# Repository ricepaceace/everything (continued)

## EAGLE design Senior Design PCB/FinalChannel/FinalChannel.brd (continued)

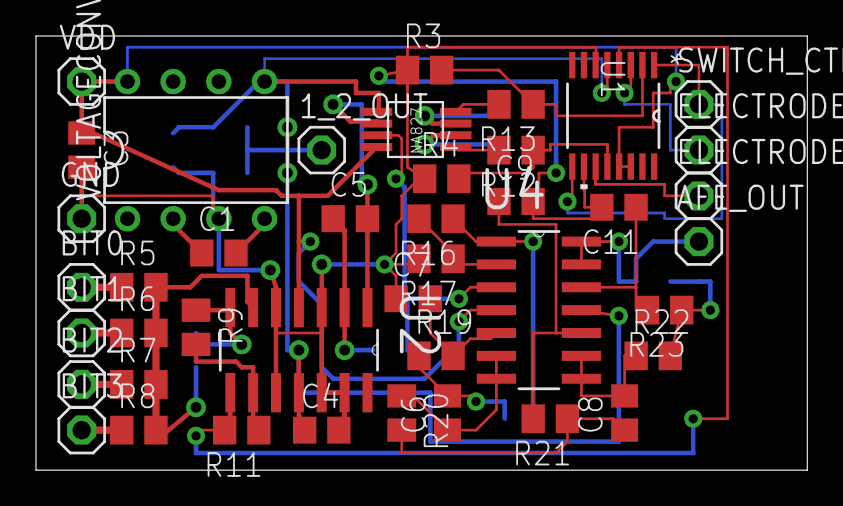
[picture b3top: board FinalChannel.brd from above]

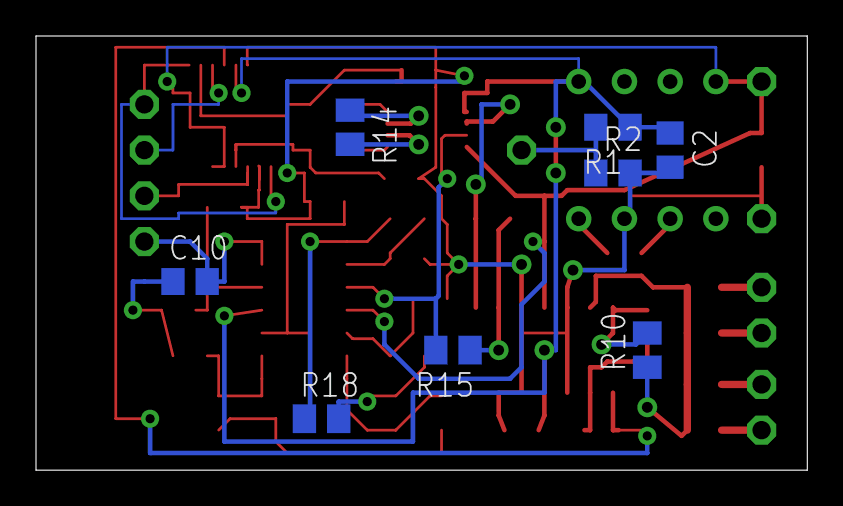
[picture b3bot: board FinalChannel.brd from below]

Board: 2 copper layers, 42.9 x 24.1 mm, 50 parts (8 on the bottom side), 37 nets.

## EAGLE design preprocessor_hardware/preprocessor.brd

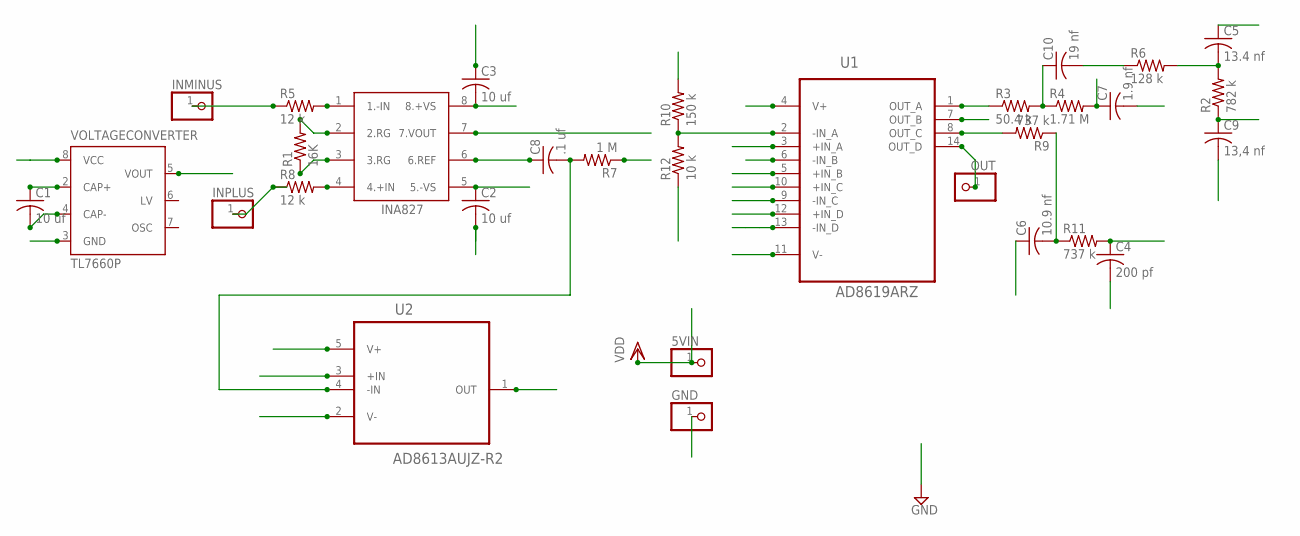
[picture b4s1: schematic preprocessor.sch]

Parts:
5VIN: PINHD-1X1; 1X01
C1, C2, C3: 10 uf; C025-025X050
C4: 200 pf; C025-025X050
C5: 13.4 nf; C025-025X050
C6: 10.9 nf; C025-025X050
C7: 1.9 nf; C025-025X050
C8: .1 uf; C025-025X050
C9: 13,4 nf; C025-025X050
C10: 19 nf; C025-025X050
GND: PINHD-1X1; 1X01
INAMP: INA827
INMINUS: PINHD-1X1; 1X01
INPLUS: PINHD-1X1; 1X01
OUT: PINHD-1X1; 1X01
R1: 16K; 0207/7
R2: 782 k; 0207/7
R3: 50.4 k; 0207/7
R4: 1.71 M; 0207/7
R5, R8: 12 k; 0207/7
R6: 128 k; 0207/7
R7: 1 M; 0207/7
R9, R11: 737 k; 0207/7
R10: 150 k; 0207/7
R12: 10 k; 0207/7
U1: AD8619ARZ; SOIC127P600X175-14N
U2: AD8613AUJZ-R2; SOT95P280X100-5N
VOLTAGECONVERTER: TL7660P; DIL08

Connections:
GND: C2.2, C3.1, C4.2, C7.2, C9.2, GND.1, R12.1, U2.3 (+IN), VOLTAGECONVERTER.3 (GND)
I3: C9.1, R2.1, U1.10 (+IN_C)
I4: C4.1, R11.2, U1.12 (+IN_D)
IAO: INAMP.7 (7.VOUT), R7.1, U1.3 (+IN_A)
IN2: C7.1, R4.2, U1.5 (+IN_B)
I_P: INPLUS.1, R8.1
unnamed: C1.1, VOLTAGECONVERTER.2 (CAP+)
unnamed: C1.2, VOLTAGECONVERTER.4 (CAP-)
unnamed: INAMP.1 (1.-IN), R5.2
unnamed: INAMP.4 (4.+IN), R8.2
unnamed: INAMP.2 (2.RG), R1.2
unnamed: INAMP.3 (3.RG), R1.1
unnamed: C8.2, R7.2, U2.4 (-IN)
unnamed: R10.1, R12.2, U1.2 (-IN_A)
unnamed: C10.1, R3.2, R4.1
unnamed: C5.2, R2.2, R6.2
unnamed: C6.2, R9.1, R11.1
unnamed: INMINUS.1, R5.1
O1: R3.1, R10.2, U1.1 (OUT_A)
O2: C10.2, R6.1, U1.6 (-IN_B), U1.7 (OUT_B)
O3: C5.1, R9.2, U1.8 (OUT_C), U1.9 (-IN_C)
OUT: C6.1, OUT.1, U1.13 (-IN_D), U1.14 (OUT_D)
REF: C8.1, INAMP.6 (6.REF), U2.1 (OUT)
VDD: 5VIN.1, C3.2, INAMP.8 (8.+VS), U1.4 (V+), U2.5 (V+), VOLTAGECONVERTER.8 (VCC)
VDD-: C2.1, INAMP.5 (5.-VS), U1.11 (V-), U2.2 (V-), VOLTAGECONVERTER.5 (VOUT)

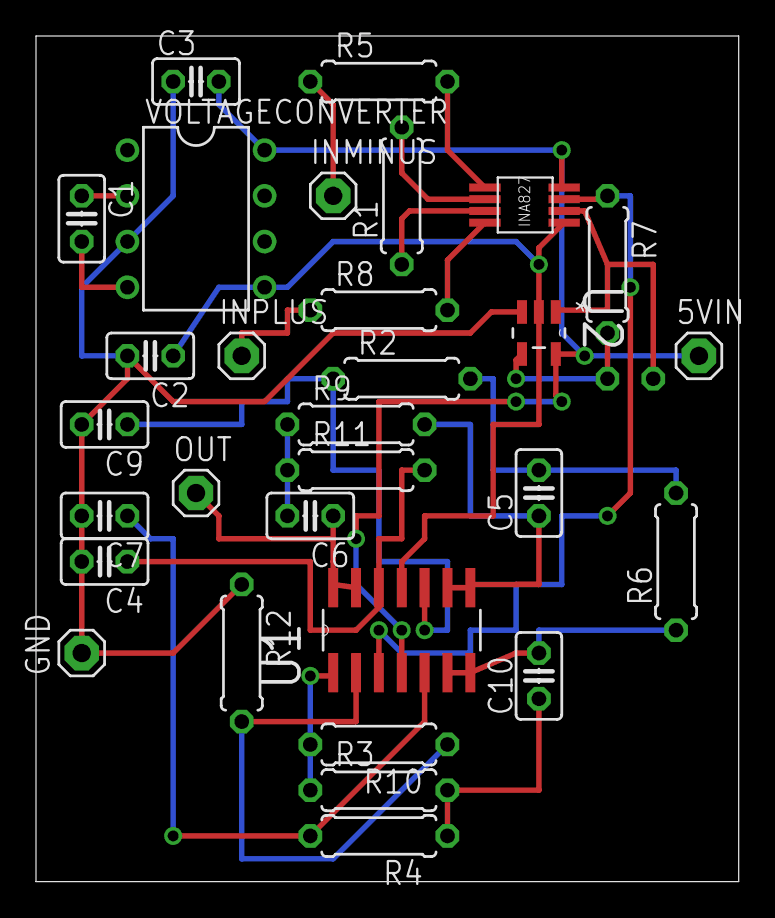
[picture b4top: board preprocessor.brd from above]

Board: 2 copper layers, 39.0 x 47.0 mm, 31 parts (1 on the bottom side), 25 nets.

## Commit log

2016-10-07 added data from sept29 test
2016-10-07 Rename multisite_detect.mat to multisite_detect.m
2016-10-12 Add files via upload
    functional code for detecting atrial and ventricular beats on data from sept29 using only the sum of the channels and set parameters.
2016-10-16 Subdivision based algorithm. Works on some channels, but not all.
2016-10-16 Added new binary search based parameter guesser. It's pretty advanced 😉
2016-10-18 Fixed problem where atrial beats were not always detected due to not big enough zeroing out of ventricular beats by increasting t_blank and l_blank.
2016-10-27 adds empty sketch for c algorithm
2016-10-27 redoes path
2016-10-27 same as previous
2016-10-27 Added channel 1 of normal sinus rythm into progmem
2016-10-27 implements one chamber peak detection
2016-10-27 Delete iaf1_afw.dat
    accessible via internet
2016-10-27 "First draft of translation for GuessParameters 2 to C code"
2016-10-28 Ported CountPeaks to C. The filter needs to be recalculated.
2016-10-28 Few lines need to be analyzed in Guessparameter function with respect to what countPeaks returns
2016-10-29 Fixed many things, but still probably won't compile.
2016-10-29 Fixed bugs. It should actually compile now.
2016-11-01 Add files via upload
    fixed .mat files
2016-11-02 testDecision.m
2016-11-02 testDecision.m
    This script takes in ECG data from a single channel, analyzes the ECG data one sample at a time (in order to best model our real time micro-controller system), and implements decision making on wheth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
2016-11-03 Fixed bug in determining where a stimulation is needed and plot where stimulation occurs for visualization
2016-11-03 fixed a bug where peaks were being over counted
2016-11-06 Added code that makes graph to see if we can get away with no fft
2016-11-06 Deleted physiobank matlab toolbox
2016-11-06 Added new flat-finding algorithm instead of binary search Modified other code to work with it
2016-11-07 Moved data files to same directory + fixed compilation errors
2016-11-07 Bug fixes
    Runs on the Arduino and gives potentially reasonable values for thresholds, but we think it is counting both A and V beats as V beats.
2016-11-11 adds schematic and board files for eagle design of preprocessor
2016-11-15 First draft of creating analog test data with arduino
2016-11-15 adds gerber files for board fabrication
2016-11-15 pushes fab design rule files for future ease of access
2016-11-15 Updated some testing code on analog test arduino file
2016-11-15 Produce analog test data from digital test data
2016-11-20 Added yamPeakFinder and MultisiteDecision
    yamPeakFinder and Multisite Decision incorporate multisite and stimulation functionality to the algirhtm.
2016-11-20 Added serial comm b/n Matlab and Arduino
2016-11-20 Added serial comm capabilities between matlab and arduino
2016-11-20 Moved file
2016-11-20 Add files via upload
    fixed a lot of bugs - still need to adapt yamPeakFinder to look more like CountPeaks (fixed in this update)
2016-11-21 Moved arduino code, fixed one bug Yamin made earlier
2016-11-22 Real time decision works - still fixing bugs with guess parameters
2016-11-22 Fixing bugs with parameter guessing
    choosing between + and - data now; still need to finish and make the same changes in real time decision
2016-11-23 Add files via upload
    added functionality of checking both + an - data
2016-11-23 Matlab code ready for porting to c
2016-11-23 Started porting guessparameters flat-finding algorithm. It may not be up to date with the newest changes.
2016-11-28 Need to add CountPeaks to this .h file
2016-11-28 adds some header files for commonly used values and types
2016-11-28 ports yamPeakFinder.m to c
2016-11-28 fixes typos
2016-11-28 Ported GuessParameters2 and BinarySearch. Added arduinocompat so that it almost compiles with regular gcc with gcc -c -DNO_ARDUINO -x c Arduino.ino
2016-11-28 moved arduino files to arduino
2016-11-28 Switched to using constants in constants.h
2016-11-29 Ported CountPeaks.m
2016-11-29 Refactored
2016-11-29 porting c code
2016-11-30 porting shit from c
2016-11-30 Added a SAMPLE_RATE, MIN_HEARTRATE, and MAX_HEARTRATE to constants.h
2016-11-30 fixing yamins mistakes
2016-12-01 Ported arduino code with the weird error implicit declaration of function
2016-12-01 It compiles!
2016-12-01 Code no runs, but thresholds calculated incorrectly, they are both 0
2016-12-02 Learning thresholds should be working on the microcontroller
2016-12-02 Finished arduinocompat.h so you can actually compile with gcc and run on a computer.
2016-12-02 Modified printed output to prepare for demoing this
2016-12-02 Made multisiteDecision run on the code. It says that the ventricle needs to be stimulated a bunch, which I think is wrong because this is supposed to be healthy heart data, but I haven't run it throu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
2016-12-05 Changed delay, added printing when it finds a beat.
2016-12-05 Added changes to how we stream analog data
2016-12-05 Switched to arduino analog
2016-12-05 Missed change in multisite decision
2016-12-05 Added buffering
2016-12-05 Changed range in matlab data
2016-12-05 Make sure to sample every milisecond when analog reading
2016-12-05 remapped analog values
2016-12-05 Try adding volatile to bufferdata
2016-12-05 Added prelearn code
2016-12-06 Fixed sampling errorgit add yamPeakFinder.h git add yamPeakFinder.h git add yamPeakFinder.h Demo is workable, can use some refinement
2016-12-07 Switched to circular buffers. Should reduce the number of dropped samples.
2016-12-09 adds all the shit for FPGA tools
2017-01-18 added pulse generator hardware schematic
2017-01-21 Added simple voting for pacing
2017-01-21 Preliminary version of polling stimulation completed
2017-01-21 Data used for learning during the first semester demo
2017-01-23 Moved matlab files to matlab folder, added gitignore
2017-01-23 Removed DS_Store
2017-01-23 Remove clutter
2017-01-26 added LearnLengths.m
    Added k-means based algorithm for learning lengths; not really integrated with anything else yet.
2017-01-26 Add files via upload
    uses LearnLengths
2017-01-27 Added simple n/2 polling to C
2017-02-02 README
    This folder will contain all the data that Dr.Greet gave us in early Feburary 2017. It should contain Sinus, atrial flutter, afib, etc.
2017-02-02 Data given to us by Dr. Greet
2017-02-08 Add files via upload
    This branch is for fixing the corner case where the atria are taller than the ventricles
2017-02-08 Update and rename GuessParameters2.m to LearnParameters.m
    uses LearnLengths and tries different lengths for +/- data
2017-02-08 Update LearnLengths.m
    outputs two lengths/chamber for +/- data
2017-02-08 Update multisite_detect.m
    now uses LearnParameters
2017-02-08 Add files via upload
    both main files now use simple versions of LearnParameters and LearnLengths that try different lengths for +/- data but always do ventricles first.
2017-02-08 Added learn lenghts except k-means
2017-02-08 Added untested kmeans
2017-02-15 length learning with k-means works! Not yet integrated though.
2017-02-15 Integrated LearnLengths, add cap to # iterations in k-means. Not sure if it works on all the channels though.
2017-02-23 Added resize to circular buffer
2017-02-26 bugfix
2017-02-27 added weighted polling and fixed overstimulation
    Re-weighting happens a fixed length of time (100ms) after the first of a potential batch of peaks is detected. Uses those 100 ms to determine if a beat occurred, figures out which channels were corre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
    Could potentially use this for stimulation decision to reduce latency by keeping track of the times of globally determined beats
2017-02-28 reorganizes stuff
2017-02-28 adds src for hls design
2017-02-28 Adds finished Vivado HLS Project, including exported IP
2017-02-28 adds screenshots from vivado HLS process
2017-02-28 removes extra screen shot
2017-02-28 adds source files for vivado and sdk, as well as full vivado project
2017-02-28 adds sdk test project to ensure all hardware components function as desired
2017-02-28 moves files around
2017-02-28 adds full system demo project
2017-02-28 commits the stuff i didn't realize wasn't included
2017-03-01 reformatted structs to match others
2017-03-01 stuff for testing/demo
2017-03-19 Add files via upload
    Successful fix of corner case in non-real-time code; started work on real-time
2017-03-20 Real time corner case fix
    It works, but not great yet - need to figure out the right way to delay the decision for the type of peak that is being evaluated second. Probably not using PreVARP/PostVARP/PreAVRP/PostAVRP correctl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
2017-03-29 Committing final arduino test code for showcase
2017-03-29 "Arduino test shit"
2017-03-31 fuck me
2017-04-06 ECE Affiliates day streaming code
2017-04-06 Added Arduino code for showcase (untested)
2017-04-06 random file update
2017-04-08 bad commit message
2017-04-08 Changed outlier removal, sign bug fixed
2017-04-08 Fixed off-by-one weighting bug in kmeans
2017-04-08 Reduced upper limit on allowed peaks to remove outliers. TODO: port statistics-based outlier removal code from Matlab
2017-04-08 Made code fit on small arduino and mega
2017-04-10 adds recent software work
2017-04-10 Fixed version for Arduino pro mini
2017-04-12 Changed Arduino code for showcase to zero out channels. Untested.
2017-04-12 Change from mask to zeroed bools
2017-04-19 Added BOMs, versions for assembly instructions
2017-04-27 Added Latex paper
2017-04-27 Changed bibliography and citations to use bibtex, other minor changes.
2017-04-27 ported more
2017-04-27 Finished porting. Updated graphs with real data
2017-04-27 Aded fpga
2017-04-27 Fixed authors
2017-04-27 More editing, schematic
2017-04-28 Philip's revisions of the first 2.75 pages
2017-04-28 Yamin's changes to matlab code that was used to generate plots for apepr
2017-04-28 Yamin's edits on the ??? and TODO
2017-04-28 Added pdf from Yamin's last edits.
2017-04-28 Made some of benhaam's recommended changes
2017-04-28 Fixed a small typo
2017-04-29 Added figure showing widths and heights.
2017-04-29 Philip finished revising
2017-04-29 adds final asic report and image
2017-04-29 Used to generate test results in our poster
    (using multisite_detect for detection accuracy and multisiteDecision for stimulation accuracy)
2017-04-29 Minor changes to paper
2017-04-29 Minor arduino changes
2017-04-29 Deleted unused files
2017-04-29 Made it more math-y
2017-04-29 Fixed some misspellings, improved next steps
2017-04-29 Added summary, minor changes to paper
2017-04-29 Added Daniel's comments
2017-04-29 Added comments and homogenized variable names
2017-04-30 Incoorperating Joe and benhaam's latest changes
2017-04-30 Fixed minor citation error and added Yamin's comments to the Matlab code
2017-05-01 Added what I could of Behnaam's changes
2017-05-01 Regorganized and documents hardware files
2017-05-01 comments code
2017-05-01 Low latency version
    This version of the code attains latencies under 50 ms, but it may struggle more if the channels are out of sync.
2017-05-01 Made some quick changes before sending Benhaam interation 3
2017-05-01 Made additional changes
2017-05-01 Made some changes to extended summary
2017-05-01 added wireless figure
2017-05-02 Commented threshold learning
